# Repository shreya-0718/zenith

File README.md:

# zenith
### An STM32-based flight controller!

I made this project to explore more advanced hardware and firmware :)
Also, to get experience with the STM32 and its IDEs.

## Features:
- USB-C 
- MicroSD Card
- Servos: Two PWM Channels
- Sensors: I²C barometer (BMP580) and charger (BQ25883), SPI IMU (ICM-45686)
- Two programmable LEDs

## To Use:
- Install STM32CubeIDE here: https://www.st.com/en/development-tools/stm32cubeide.html
- Use the code in here as a starter, and build from there!
- Use the schematic below as a guide.

## Images:

<br>

<br>

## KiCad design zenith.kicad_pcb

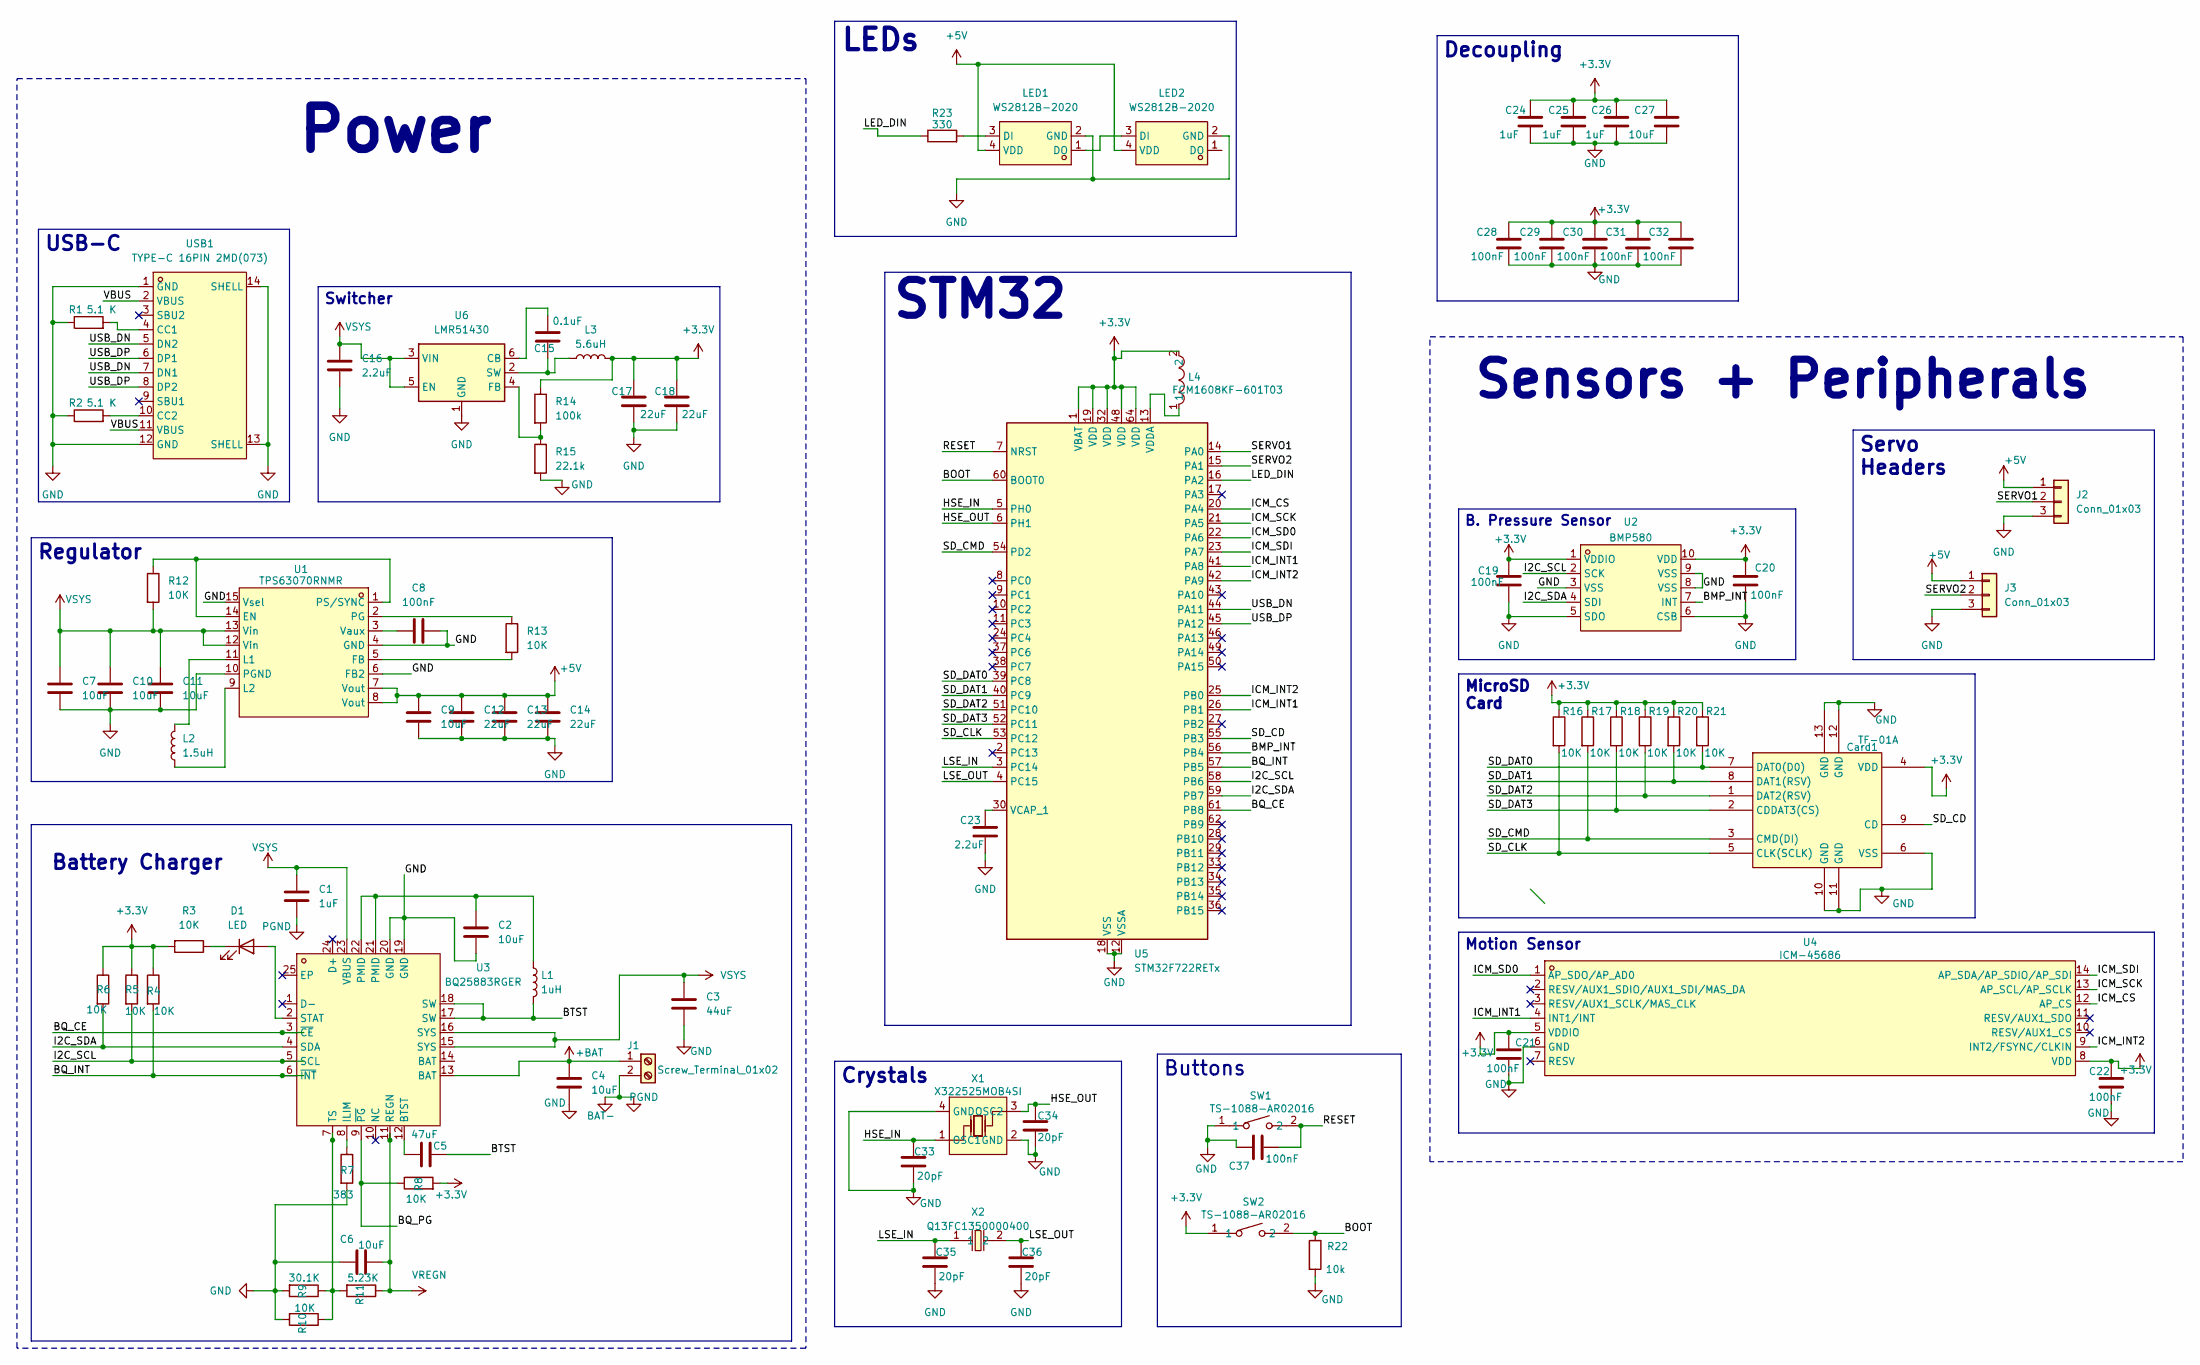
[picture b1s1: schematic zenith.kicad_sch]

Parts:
C1, C24, C25, C26: 1uF; C_0402_1005Metric
C2, C4, C6, C7, C9, C10, C11, C27: 10uF; C_0402_1005Metric
C3: 44uF; C_0805_2012Metric
C5: 47uF; C_0805_2012Metric
C8, C19, C20, C21, C22, C28, C29, C30, C31, C32, C37: 100nF; C_0201_0603Metric
C12, C13, C14, C17, C18: 22uF; C_0805_2012Metric
C15: 0.1uF; C_0201_0603Metric
C16, C23: 2.2uF; C_0402_1005Metric
C33, C34, C35, C36: 20pF; C_0201_0603Metric
Card1: TF-01A; TF-SMD_TF-01A; LCSC Part C91145
D1: LED; LED_0402_1005Metric
J1: Screw_Terminal_01x02; TerminalBlock_Xinya_XY308-2.54-2P_1x02_P2.54mm_Horizontal
J2, J3: Conn_01x03; PinHeader_1x03_P2.54mm_Vertical
L1: 1uH; L2520
L2: 1.5uH; IND-SMD_L4.0-W4.0-A
L3: 5.6uH; IND-SMD_L3.0-W3.0
L4: FCM1608KF-601T03; L0603; LCSC Part C141723
LED1, LED2: WS2812B-2020; LED-SMD_4P-L2.0-W2.0-TL_WS2812B-2020; LCSC Part C965555
R1, R2: 5.1 K; R_0201_0603Metric
R3, R4, R5, R6, R8, R10, R12, R13, R16, R17, R18, R19, R20, R21: 10K; R_0201_0603Metric
R7: 383; R_0201_0603Metric
R9: 30.1K; R_0201_0603Metric
R11: 5.23K; R_0201_0603Metric
R14: 100k; R_0402_1005Metric
R15: 22.1k; R_0201_0603Metric
R22: 10k; R_0201_0603Metric
R23: 330; R_0201_0603Metric
SW1, SW2: TS-1088-AR02016; SW-SMD_L3.9-W3.0-P4.45; LCSC Part C720477
U1: TPS63070RNMR; VQFN-HR-15_L3.0-W2.5-P0.50-BL_TPS63070RNMR; LCSC Part C109322
U2: BMP580; LGA-10_L2.0-W2.0-P0.50-TL_BMP580; LCSC Part C22391138
U3: BQ25883RGER; VFQFPN-24_L4.0-W4.0-P0.50-BL-EP2.8; LCSC Part C544362
U4: ICM-45686; LGA-14_L3.0-W2.5-P0.50-TL; LCSC Part C22459454
U5: STM32F722RETx; LQFP-64_10x10mm_P0.5mm
U6: LMR51430; SOT-23-6
USB1: TYPE-C 16PIN 2MD(073); USB-C-SMD_TYPE-C-6PIN-2MD-073; LCSC Part C2765186
X1: X322525MOB4SI; CRYSTAL-SMD_4P-L3.2-W2.5-BL; LCSC Part C9006
X2: Q13FC1350000400; FC-135R_L3.2-W1.5; LCSC Part C32346

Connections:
+3.3V: C17.1, C18.1, C19.1, C20.1, C21.1, C22.1, C24.1, C25.1, C26.1, C27.1, C28.1, C29.1, C30.1, C31.1, C32.1, Card1.4 (VDD), L3.2, L4.2, R3.2, R4.1, R5.1, R6.1, R8.2, R14.1, R16.1, R17.1, R18.1, R19.1, R20.1, R21.1, SW2.1, U2.1 (VDDIO), U2.10 (VDD), U4.5 (VDDIO), U4.8 (VDD), U5.1 (VBAT), U5.19 (VDD), U5.32 (VDD), U5.48 (VDD), U5.64 (VDD); also elsewhere on the board
+5V: C9.1, C12.1, C13.1, C14.1, J2.1, J3.1, LED1.4 (VDD), LED2.4 (VDD), U1.7 (Vout), U1.8 (Vout); also elsewhere on the board
+BAT: C4.1, J1.1, U3.13 (BAT)
/BMP_INT: U2.7 (INT), U5.56 (PB4)
/BOOT: R22.1, SW2.2, U5.60 (BOOT0); also elsewhere on the board
/BQ_CE: U3.3 (~CE), U5.61 (PB8)
/BQ_INT: R4.2, U3.6 (~INT), U5.57 (PB5)
/BQ_PG: R8.1, U3.9 (~PG)
/BTST: C5.2, L1.2, U3.17 (SW), U3.18 (SW)
/HSE_IN: C33.1, U5.5 (PH0), X1.1 (OSC1)
/HSE_OUT: C34.1, U5.6 (PH1), X1.3 (OSC2)
/I2C_SCL: R5.2, U2.2 (SCK), U3.5 (SCL), U5.58 (PB6)
/I2C_SDA: R6.2, U2.4 (SDI), U3.4 (SDA), U5.59 (PB7)
/ICM_CS: U4.12 (AP_CS), U5.20 (PA4)
/ICM_INT1: U4.4 (INT1/INT), U5.26 (PB1), U5.41 (PA8)
/ICM_INT2: U4.9 (INT2/FSYNC/CLKIN), U5.25 (PB0), U5.42 (PA9)
/ICM_SCK: U4.13 (AP_SCL/AP_SCLK), U5.21 (PA5)
/ICM_SD0: U4.1 (AP_SDO/AP_AD0), U5.22 (PA6)
/ICM_SDI: U4.14 (AP_SDA/AP_SDIO/AP_SDI), U5.23 (PA7)
/LED_DIN: R23.1, U5.16 (PA2)
/LSE_IN: C35.1, U5.3 (PC14), X2.1
/LSE_OUT: C36.1, U5.4 (PC15), X2.2
/RESET: C37.2, SW1.2, U5.7 (NRST); also elsewhere on the board
/SD_CD: Card1.9 (CD), U5.55 (PB3); also elsewhere on the board
/SD_CLK: Card1.5 (CLK(SCLK)), R16.2, U5.53 (PC12); also elsewhere on the board
/SD_CMD: Card1.3 (CMD(DI)), R17.2, U5.54 (PD2); also elsewhere on the board
/SD_DAT0: Card1.7 (DAT0(D0)), R21.2, U5.39 (PC8); also elsewhere on the board
/SD_DAT1: Card1.8 (DAT1(RSV)), R20.2, U5.40 (PC9); also elsewhere on the board
/SD_DAT2: Card1.1 (DAT2(RSV)), R19.2, U5.51 (PC10); also elsewhere on the board
/SD_DAT3: Card1.2 (CDDAT3(CS)), R18.2, U5.52 (PC11); also elsewhere on the board
/SERVO1: J2.2, U5.14 (PA0)
/SERVO2: J3.2, U5.15 (PA1); also elsewhere on the board
/USB_DN: U5.44 (PA11), USB1.5 (DN2), USB1.7 (DN1)
/USB_DP: U5.45 (PA12), USB1.6 (DP1), USB1.8 (DP2)
/VBUS: USB1.2 (VBUS), USB1.11 (VBUS)
BAT-: C1.1, J1.2
GND: C2.2, C3.2, C4.2, C6.1, C7.2, C8.2, C9.2, C10.2, C11.2, C12.2, C13.2, C14.2, C16.2, C17.2, C18.2, C19.2, C20.2, C21.2, C22.2, C23.2, C24.2, C25.2, C26.2, C27.2, C28.2, C29.2, C30.2, C31.2, C32.2, C33.2, C34.2, C35.2, C36.2, C37.1, Card1.6 (VSS), Card1.10 (GND), Card1.11 (GND), Card1.12 (GND), Card1.13 (GND), J2.3, J3.3, LED1.2 (GND), LED2.2 (GND), R1.1, R2.1, R7.2, R9.2, R10.2, R15.2, R22.2, SW1.1, U1.4 (GND), U1.6 (FB2), U1.10 (PGND), U1.15 (Vsel), U2.3 (VSS), U2.5 (SDO), U2.6 (CSB), U2.8 (VSS), U2.9 (VSS), U3.19 (GND), U3.20 (GND), U4.6 (GND), U5.12 (VSSA), U5.18 (VSS), U5.31 (VSS), U5.47 (VSS), U5.63 (VSS), U6.1 (GND), USB1.1 (GND), USB1.12 (GND), USB1.13 (SHELL), USB1.14 (SHELL), X1.2 (GND), X1.4 (GND); also elsewhere on the board
unnamed: C2.1, L1.1, U3.21 (PMID), U3.22 (PMID)
unnamed: D1.2 (A), U3.2 (STAT)
unnamed: D1.1 (K), R3.1
unnamed: LED1.3 (DI), R23.2
unnamed: LED1.1 (DO), LED2.3 (DI)
unnamed: R12.1, U1.1 (PS/SYNC), U1.14 (EN)
unnamed: R13.2, U1.5 (FB)
unnamed: L2.2, U1.11 (L1)
unnamed: L2.1, U1.9 (L2)
unnamed: R13.1, U1.2 (PG)
unnamed: C8.1, U1.3 (Vaux)
unnamed: C5.1, U3.12 (BTST)
unnamed: R7.1, U3.8 (ILIM)
unnamed: R9.1, R10.1, R11.2, U3.7 (TS)
unnamed: C23.1, U5.30 (VCAP_1)
unnamed: L4.1, U5.13 (VDDA)
unnamed: C15.1, U6.6 (CB)
unnamed: R14.2, R15.1, U6.4 (FB)
unnamed: C15.2, L3.1, U6.2 (SW)
unnamed: R1.2, USB1.4 (CC1)
unnamed: R2.2, USB1.10 (CC2)
VREGN: C6.2, R11.1, U3.11 (REGN)
VSYS: C1.2, C3.1, C7.1, C10.1, C11.1, C16.1, R12.2, U1.12 (Vin), U1.13 (Vin), U3.15 (SYS), U3.16 (SYS), U3.23 (VBUS), U6.3 (VIN), U6.5 (EN)

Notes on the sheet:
Power
Battery Charger
Sensors + Peripherals
LEDs
Crystals
USB-C
MicroSD Card
Decoupling
B. Pressure Sensor
Buttons
Servo Headers
Motion Sensor
Switcher
STM32
Regulator

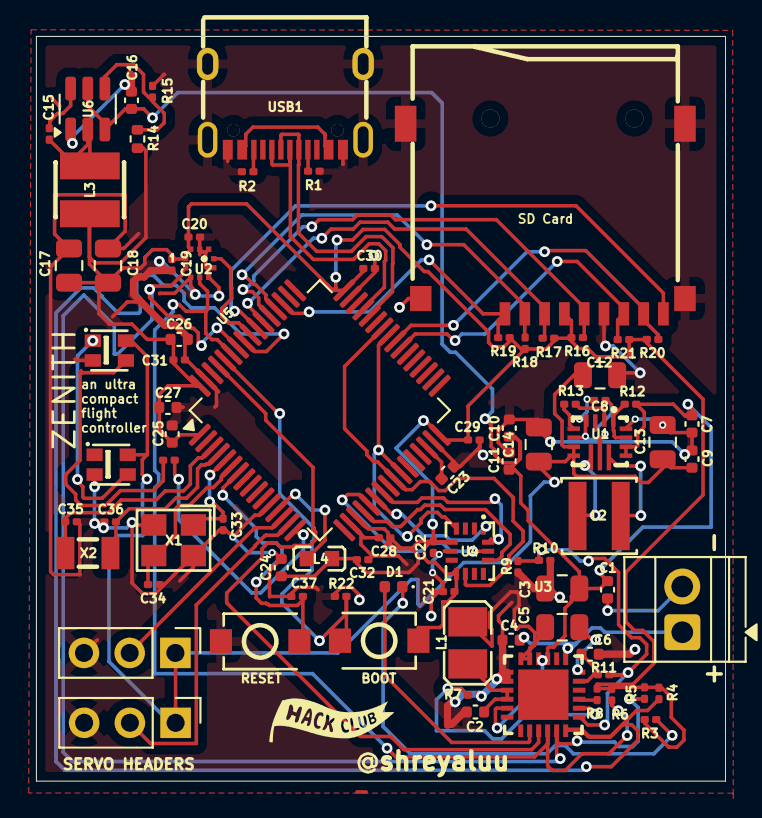
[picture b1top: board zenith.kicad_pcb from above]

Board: 2 copper layers, 38.3 x 41.4 mm, 82 parts (0 on the bottom side), 60 nets.

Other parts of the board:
BOOT: TS-1088-AR02016; SW-SMD_L3.9-W3.0-P4.45
RESET: TS-1088-AR02016; SW-SMD_L3.9-W3.0-P4.45
SD Card: TF-01A; TF-SMD_TF-01A
SERVO HEADERS: Conn_01x03; PinHeader_1x03_P2.54mm_Vertical

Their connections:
+3.3V: BOOT.1, SD Card.4 (VDD); also elsewhere on the board
+5V: SERVO HEADERS.1; also elsewhere on the board
/BOOT: BOOT.2; also elsewhere on the board
/RESET: RESET.2; also elsewhere on the board
/SD_CD: SD Card.9 (CD); also elsewhere on the board
/SD_CLK: SD Card.5 (CLK(SCLK)); also elsewhere on the board
/SD_CMD: SD Card.3 (CMD(DI)); also elsewhere on the board
/SD_DAT0: SD Card.7 (DAT0(D0)); also elsewhere on the board
/SD_DAT1: SD Card.8 (DAT1(RSV)); also elsewhere on the board
/SD_DAT2: SD Card.1 (DAT2(RSV)); also elsewhere on the board
/SD_DAT3: SD Card.2 (CDDAT3(CS)); also elsewhere on the board
/SERVO2: SERVO HEADERS.2; also elsewhere on the board
GND: RESET.1, SD Card.6 (VSS), SD Card.10 (GND), SD Card.11 (GND), SD Card.12 (GND), SD Card.13 (GND), SERVO HEADERS.3; also elsewhere on the board

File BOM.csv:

"Id";"Designator";"Footprint";"Quantity";"Designation";"Supplier and ref";
1;"U2";"LGA-10_L2.0-W2.0-P0.50-TL_BMP580";1;"BMP580";;;
2;"R23";"R_0201_0603Metric";1;"330";;;
3;"LED2,LED1";"LED-SMD_4P-L2.0-W2.0-TL_WS2812B-2020";2;"WS2812B-2020";;;
4;"C26,C24,C1,C25";"C_0402_1005Metric";4;"1uF";;;
5;"R2,R1";"R_0201_0603Metric";2;"5.1 K";;;
6;"R20,R21,R12,R5,R13,R16,R19,R10,R4,R17,R8,R3,R18,R6";"R_0201_0603Metric";14;"10K";;;
7;"C30,C20,C32,C8,C19,C37,C22,C28,C29,C21,C31";"C_0201_0603Metric";11;"100nF";;;
8;"C3";"C_0805_2012Metric";1;"44uF";;;
9;"C9,C2,C7,C10,C27,C4,C6,C11";"C_0402_1005Metric";8;"10uF";;;
10;"U4";"LGA-14_L3.0-W2.5-P0.50-TL";1;"ICM-45686";;;
11;"BOOT,RESET";"SW-SMD_L3.9-W3.0-P4.45";2;"TS-1088-AR02016";;;
12;"C15";"C_0201_0603Metric";1;"0.1uF";;;
13;"R14";"R_0402_1005Metric";1;"100k";;;
14;"L1";"L2520";1;"1uH";;;
15;"C17,C13,C12,C18,C14";"C_0805_2012Metric";5;"22uF";;;
16;"J1";"TerminalBlock_Xinya_XY308-2.54-2P_1x02_P2.54mm_Horizontal";1;"Screw_Terminal_01x02";;;
17;"SERVO HEADERS,J2";"PinHeader_1x03_P2.54mm_Vertical";2;"Conn_01x03";;;
18;"C16,C23";"C_0402_1005Metric";2;"2.2uF";;;
19;"R15";"R_0201_0603Metric";1;"22.1k";;;
20;"X1";"CRYSTAL-SMD_4P-L3.2-W2.5-BL";1;"X322525MOB4SI";;;
21;"U3";"VFQFPN-24_L4.0-W4.0-P0.50-BL-EP2.8";1;"BQ25883RGER";;;
22;"D1";"LED_0402_1005Metric";1;"LED";;;
23;"SD Card";"TF-SMD_TF-01A";1;"TF-01A";;;
24;"R11";"R_0201_0603Metric";1;"5.23K";;;
25;"C5";"C_0805_2012Metric";1;"47uF";;;
26;"C36,C35,C33,C34";"C_0201_0603Metric";4;"20pF";;;
27;"R22";"R_0201_0603Metric";1;"10k";;;
28;"U6";"SOT-23-6";1;"LMR51430";;;
29;"R9";"R_0201_0603Metric";1;"30.1K";;;
30;"X2";"FC-135R_L3.2-W1.5";1;"Q13FC1350000400";;;
31;"L4";"L0603";1;"FCM1608KF-601T03";;;
32;"U5";"LQFP-64_10x10mm_P0.5mm";1;"STM32F722RETx";;;
33;"L2";"IND-SMD_L4.0-W4.0-A";1;"1.5uH";;;
34;"L3";"IND-SMD_L3.0-W3.0";1;"5.6uH";;;
35;"USB1";"USB-C-SMD_TYPE-C-6PIN-2MD-073";1;"TYPE-C 16PIN 2MD(073)";;;
36;"R7";"R_0201_0603Metric";1;"383";;;

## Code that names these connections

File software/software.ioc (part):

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Mcu.Name=STM32F722R(C-E)Tx
Mcu.Package=LQFP64
Mcu.UserName=STM32F722RETx
PA0-WKUP.Signal=S_TIM2_CH1_ETR
PA1.Signal=S_TIM2_CH2
PA11.Mode=Host_Only
PA11.Signal=USB_OTG_FS_DM
PA12.Mode=Host_Only
PA12.Signal=USB_OTG_FS_DP
PA2.Signal=GPIO_Output
PA4.Mode=NSS_Signal_Hard_Output
PA4.Signal=SPI1_NSS
PA5.Mode=Full_Duplex_Master
PA5.Signal=SPI1_SCK
PA6.Mode=Full_Duplex_Master
PA6.Signal=SPI1_MISO
PA7.Mode=Full_Duplex_Master
PA7.Signal=SPI1_MOSI
PB0.GPIOParameters=GPIO_Label
PB0.GPIO_Label=ICM_INT2
PB0.Signal=GPXTI0
PB1.GPIOParameters=GPIO_Label
PB1.GPIO_Label=ICM_INT1
PB1.Signal=GPXTI1
PB3.GPIOParameters=GPIO_Label
PB3.GPIO_Label=SD_CS
PB3.Signal=GPIO_Input
PB4.GPIOParameters=GPIO_Label
PB4.GPIO_Label=BMP_INT
PB4.Signal=GPXTI4
PB5.GPIOParameters=GPIO_Label
PB5.GPIO_Label=BQ_INT
PB5.Signal=GPXTI5
PB6.Mode=I2C
PB6.Signal=I2C1_SCL
PB7.Mode=I2C
PB7.Signal=I2C1_SDA
PB8.GPIOParameters=GPIO_Label
PB8.GPIO_Label=BQ_CE
PB8.Signal=GPIO_Output
PC10.Mode=SD_4_bits_Wide_bus
PC10.Signal=SDMMC1_D2
PC11.Mode=SD_4_bits_Wide_bus
PC11.Signal=SDMMC1_D3
PC12.Mode=SD_4_bits_Wide_bus
PC12.Signal=SDMMC1_CK
PC14-OSC32_IN.Mode=LSE-External-Oscillator
PC14-OSC32_IN.Signal=RCC_OSC32_IN
PC15-OSC32_OUT.Mode=LSE-External-Oscillator
PC15-OSC32_OUT.Signal=RCC_OSC32_OUT
PC8.Mode=SD_4_bits_Wide_bus
PC8.Signal=SDMMC1_D0
PC9.Mode=SD_4_bits_Wide_bus
PC9.Signal=SDMMC1_D1
PD2.Mode=SD_4_bits_Wide_bus
PD2.Signal=SDMMC1_CMD
PH0-OSC_IN.Mode=HSE-External-Oscillator
PH0-OSC_IN.Signal=RCC_OSC_IN
PH1-OSC_OUT.Mode=HSE-External-Oscillator
PH1-OSC_OUT.Signal=RCC_OSC_OUT
RCC.HSE_VALUE=25000000
board=custom

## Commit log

2025-11-22 added needed parts to folders
2025-11-22 wired more of the schematic, added some more parts
2025-11-22 organization, more wires!
2025-11-23 finished schematic
2025-11-23 placed components, began routing
2025-11-23 finished pcb
2025-11-24 added LEDs, finished pcb
2025-11-24 minor fixes
2025-11-24 more editing silkscreen
2025-11-24 organizing repo
2025-11-24 fixed .gitignore issues
2025-11-24 fixed gitignore issues
2025-11-24 remove extra pcb file
2025-11-24 take gitattributes out of repo
2025-11-27 installed basics for stm32 code
2025-11-28 learning basic stm32 code
2025-11-28 Add images to README for flight controller
2025-11-29 basic firmware
2025-11-29 added production files
2025-11-29 updated bom
2025-11-29 updating readme
